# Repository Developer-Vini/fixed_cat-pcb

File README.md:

# Gato PCB

A printed circuit board (PCB) project developed in KiCad.

## Project Overview

A cat-themed PCB designed for the Hack Club Solder workshop. The board features LEDs, resistors, push buttons, a battery holder, a potentiometer, a capacitor, and a motor/pinheader connector — a hands-on beginner-friendly circuit for learning PCB design and soldering.

### Circuit Components

- **2x LED** — Visual indicators
- **2x Push Switch** — User input / interaction
- **2x Resistor** — Current limiting
- **1x Potentiometer** — Adjustable resistance / brightness control
- **1x Capacitor (10uF)** — Filtering / energy storage
- **1x Motor/PinHeader** — Motor driver interface
- **1x Battery Cell** — Power supply

## Visualizations

### UPDATE PCB SKILLSCREEN

### Schematic

### PCB Layout

### PCB Front View

### PCB Back View

### 3D View

---

## Bill of Materials (BOM)

| Ref | Qty | Component | Footprint |
|-----|-----|-----------|-----------|
| BT2 | 1 | Battery Cell | BatteryHolder_Keystone_3034_1x20mm |
| C2 | 1 | Capacitor (10uF) | CP_Radial_D8.0mm_P5.00mm |
| D3, D4 | 2 | LED | LED_D5.0mm |
| M2 | 1 | Motor/PinHeader | PinHeader_1x02_P2.54mm_Vertical |
| R4 | 1 | Potentiometer | Potentiometer_Vishay_T73YP_Vertical |
| R5, R6 | 2 | Resistor (R) | R_Axial_DIN0207_L6.3mm_D2.5mm_P7.62mm_Horizontal |
| SW3, SW4 | 2 | Push Switch | SW_PUSH_6mm |

*Full BOM available in [hardware/bom/gato-pcb.csv](hardware/bom/gato-pcb.csv)*

---

### Manufacturing

Gerber files for PCB fabrication are located in `hardware/gerbers/`. These include:
- Copper layers (F_Cu, B_Cu)
- Solder mask (F_Mask, B_Mask)
- Silkscreen (F_Silkscreen, B_Silkscreen)
- Edge cuts
- Drill files (PTH, NPTH)

## Author

- **Display Name:** Vini
- **Slack Username:** `o_dev`

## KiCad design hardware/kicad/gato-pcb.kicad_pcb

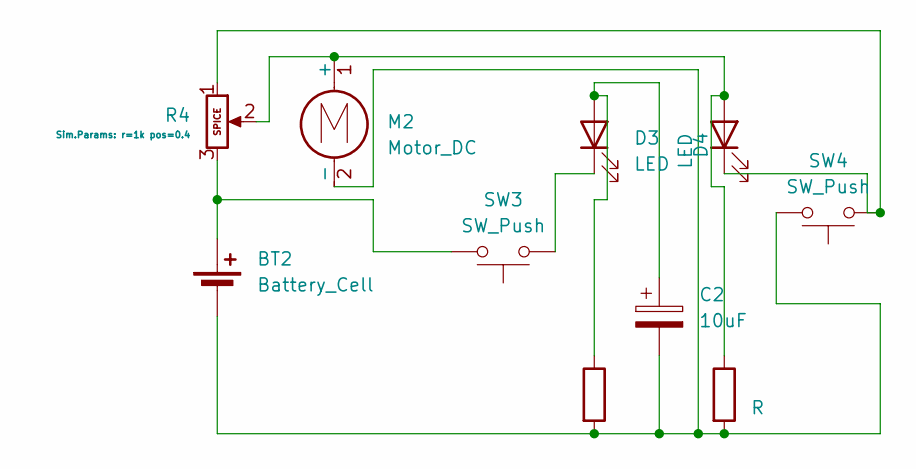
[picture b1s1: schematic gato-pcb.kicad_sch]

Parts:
BT2: Battery_Cell; BatteryHolder_Keystone_3034_1x20mm
C2: 10uF; CP_Radial_D8.0mm_P5.00mm
D3, D4: LED; LED_D5.0mm
M2: Motor_DC; PinHeader_1x02_P2.54mm_Vertical
R4: Potentiometer; Potentiometer_Vishay_T73YP_Vertical
R5, R6: R; R_Axial_DIN0207_L6.3mm_D2.5mm_P7.62mm_Horizontal
SW3, SW4: SW_Push; SW_PUSH_6mm

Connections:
unnamed: BT2.1 (+), R4.3, SW3.2
unnamed: BT2.2 (-), C2.2, M2.2 (-), R5.2, R6.2, SW4.2
unnamed: C2.1, D3.2 (A), R5.1
unnamed: D3.1 (K), SW3.1
unnamed: D4.2 (A), M2.1 (+), R4.2, R6.1
unnamed: D4.1 (K), R4.1, SW4.1

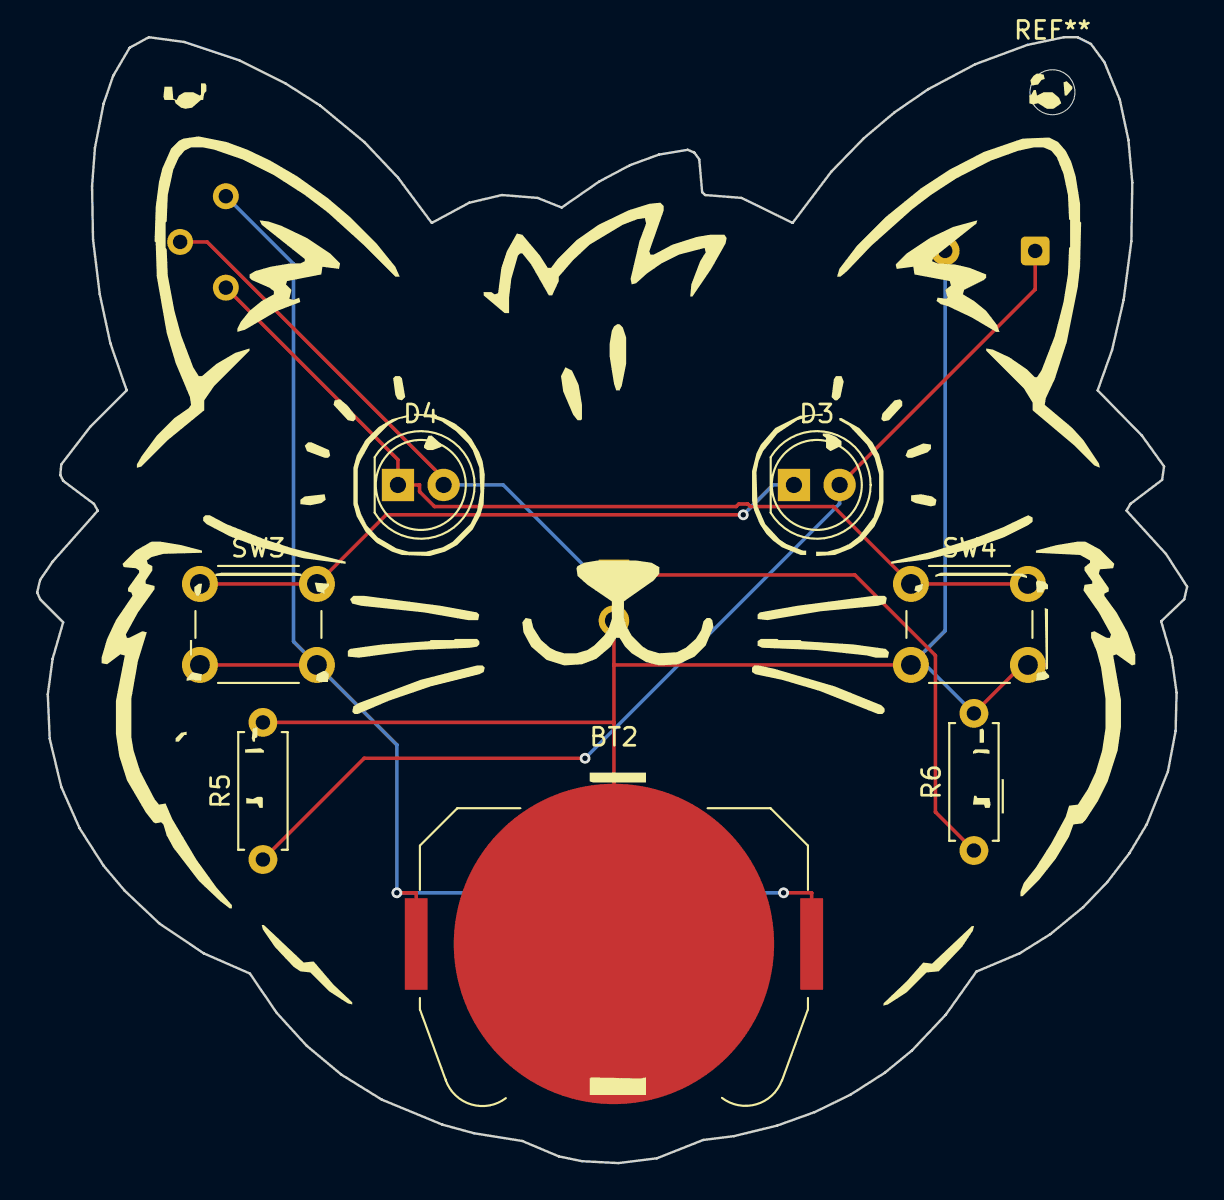
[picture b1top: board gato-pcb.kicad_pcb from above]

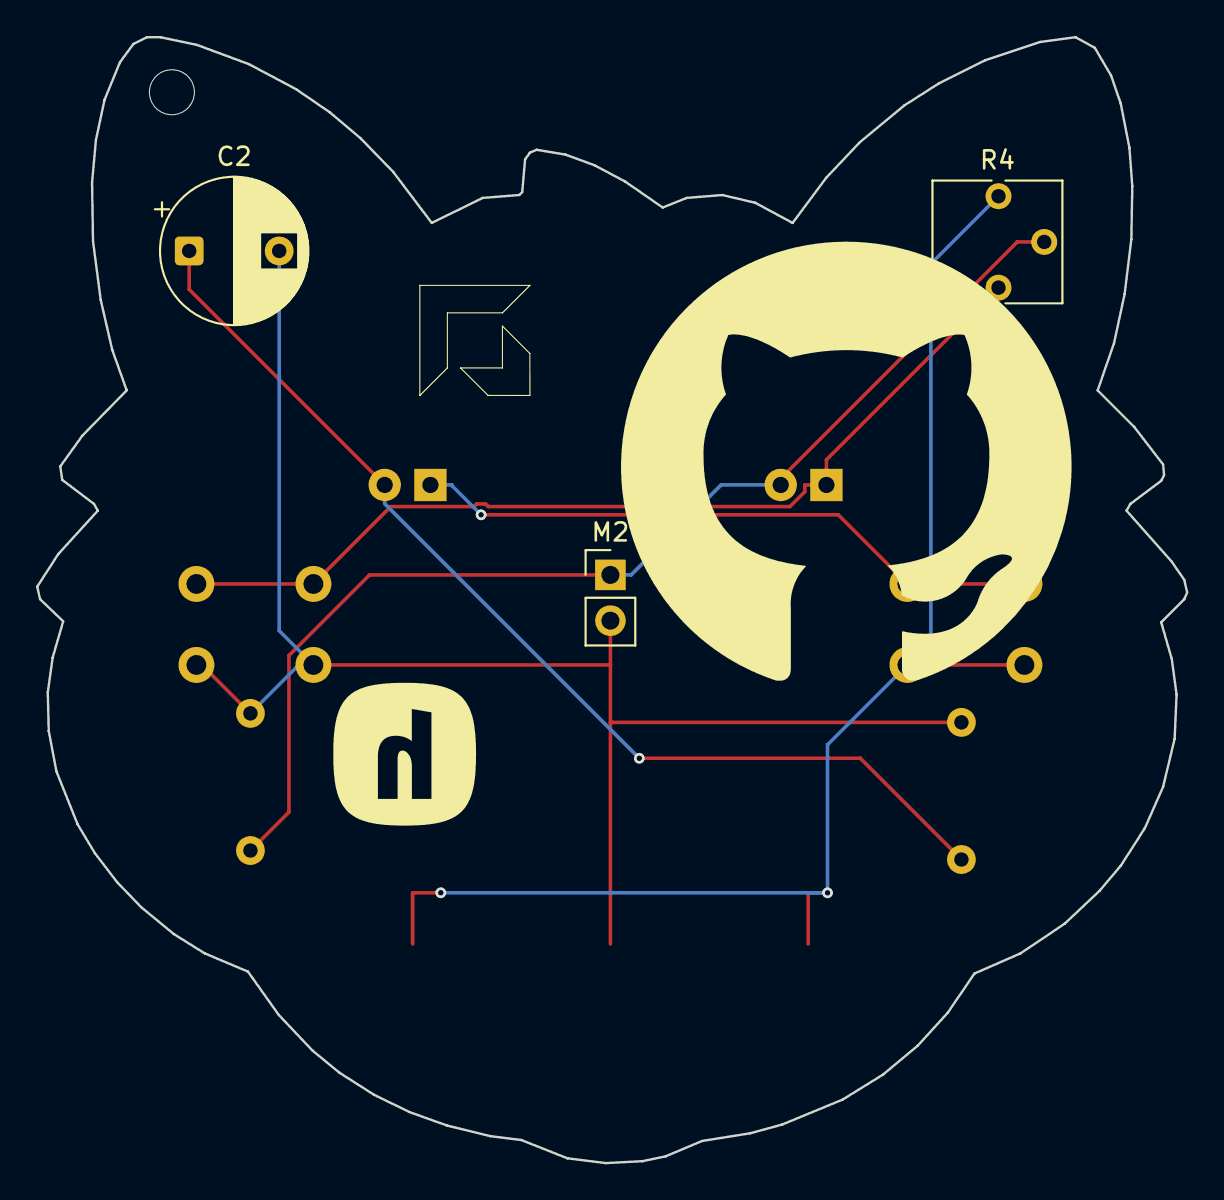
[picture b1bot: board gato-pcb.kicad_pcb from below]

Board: 2 copper layers, 63.9 x 62.5 mm, 10 parts (3 on the bottom side), 6 nets.
